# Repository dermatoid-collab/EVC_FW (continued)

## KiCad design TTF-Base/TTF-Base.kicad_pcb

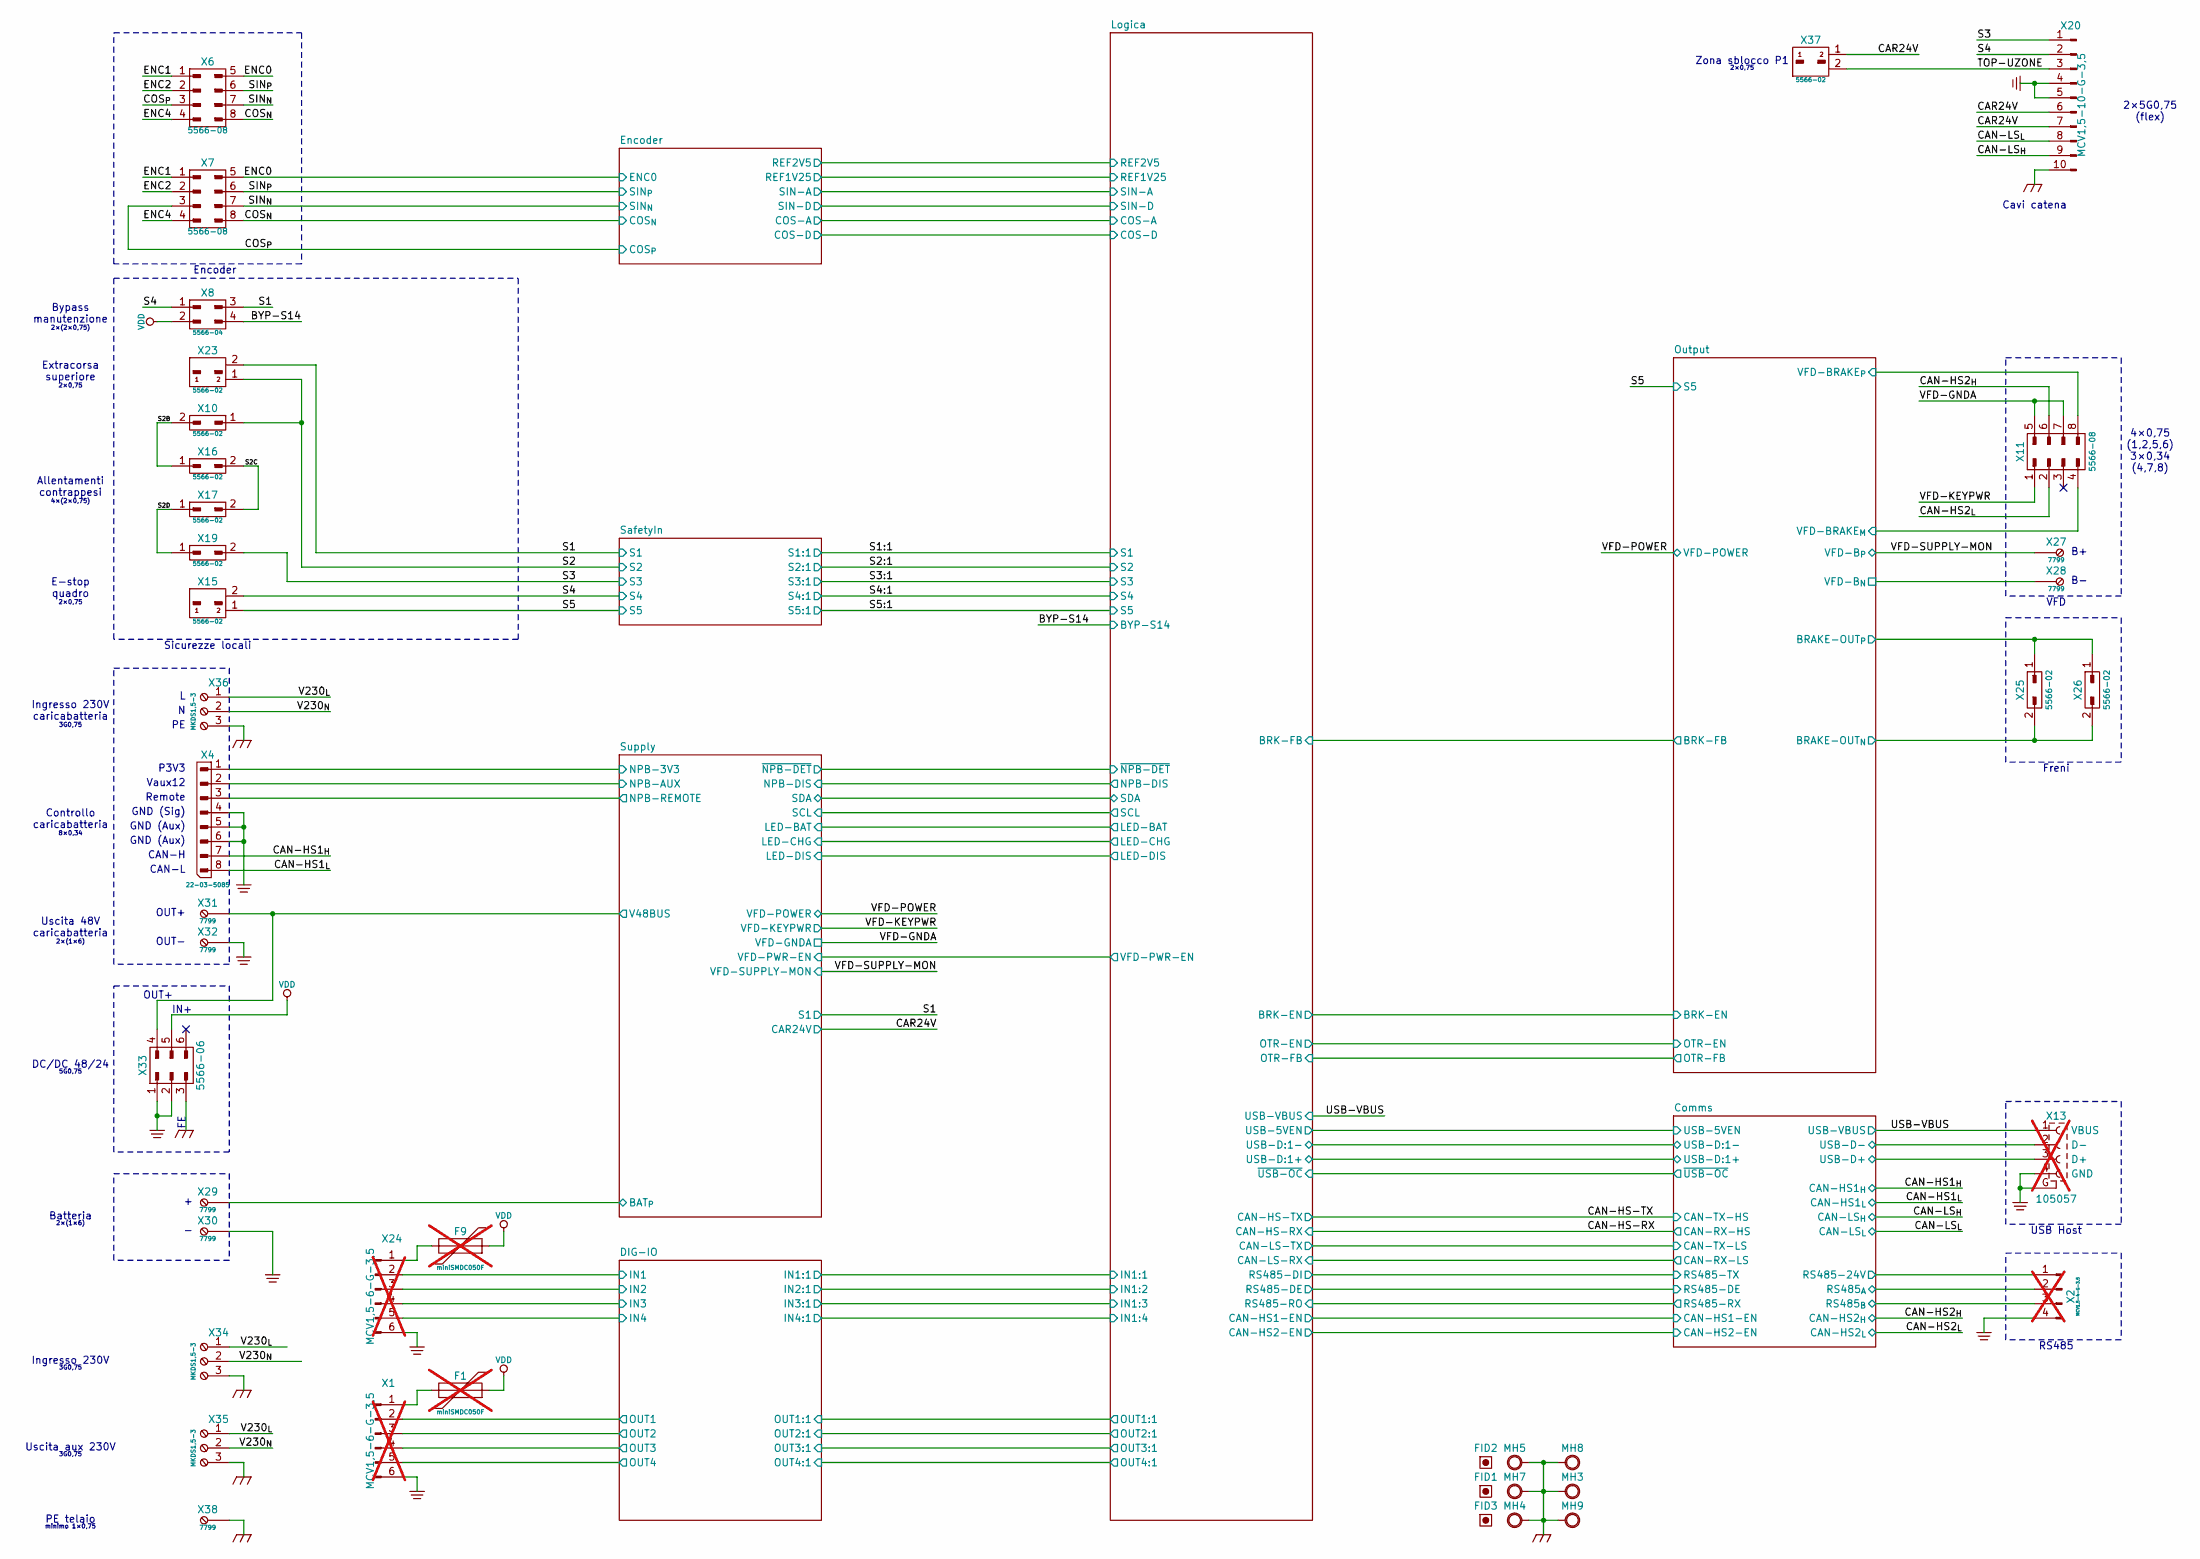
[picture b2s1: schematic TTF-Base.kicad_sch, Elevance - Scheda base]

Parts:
F1, F9: miniSMDC050F; miniSMDC; not fitted
FID1, FID2, FID3: Fiducial; Fid-10
MH3, MH4, MH5, MH7, MH8, MH9: Hole; Hole-M4
X1, X24: MCV1,5-6-G-3,5; not fitted
X2: MCV1,5-4-G-3,5; not fitted
X4: 22-03-5085
X6, X7, X11: 5566-08
X8: 5566-04
X10, X15, X16, X17, X19, X23, X25, X26, X37: 5566-02
X13: 105057; Molex-105057; not fitted
X20: MCV1,5-10-G-3,5
X27, X28, X29, X30, X31, X32, X38: 7799; Keystone-7799
X33: 5566-06
X34, X35, X36: MKDS1,5-3

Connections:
/BYP-S14: X8.4; also elsewhere on the board
/CAN-HS1_{H}: X4.7; also elsewhere on the board
/CAN-HS1_{L}: X4.8; also elsewhere on the board
/CAN-HS2_{H}: X11.6; also elsewhere on the board
/CAN-HS2_{L}: X11.2; also elsewhere on the board
/CAN-LS_{H}: X20.9; also elsewhere on the board
/CAN-LS_{L}: X20.8; also elsewhere on the board
/CAR24V: X20.6, X20.7, X37.1; also elsewhere on the board
/COS_{N}: X6.8, X7.8; also elsewhere on the board
/COS_{P}: X6.3, X7.3; also elsewhere on the board
/Comms/RS485-24V: X2.1; also elsewhere on the board
/Comms/RS485_{A}: X2.2; also elsewhere on the board
/Comms/RS485_{B}: X2.3; also elsewhere on the board
/Comms/USB-D+: X13.3 (D+); also elsewhere on the board
/Comms/USB-D-: X13.2 (D-); also elsewhere on the board
/DIG-IO/IN1: X24.2; also elsewhere on the board
/DIG-IO/IN2: X24.3; also elsewhere on the board
/DIG-IO/IN3: X24.4; also elsewhere on the board
/DIG-IO/IN4: X24.5; also elsewhere on the board
/DIG-IO/OUT1: X1.2; also elsewhere on the board
/DIG-IO/OUT2: X1.3; also elsewhere on the board
/DIG-IO/OUT3: X1.4; also elsewhere on the board
/DIG-IO/OUT4: X1.5; also elsewhere on the board
/ENC0: X6.5, X7.5; also elsewhere on the board
/ENC1: X6.1, X7.1
/ENC2: X6.2, X7.2
/ENC4: X6.4, X7.4
/Output/BRAKE-OUT_{N}: X25.2, X26.2; also elsewhere on the board
/Output/BRAKE-OUT_{P}: X25.1, X26.1; also elsewhere on the board
/Output/VFD-BRAKE_{M}: X11.4; also elsewhere on the board
/Output/VFD-BRAKE_{P}: X11.8; also elsewhere on the board
/Output/VFD-B_{N}: X28.1 (1_1); also elsewhere on the board
/S1: X8.3, X23.2; also elsewhere on the board
/S2: X10.1, X23.1; also elsewhere on the board
/S2B: X10.2, X16.1
/S2C: X16.2, X17.2
/S2D: X17.1, X19.1
/S3: X19.2, X20.1; also elsewhere on the board
/S4: X8.1, X15.2, X20.2; also elsewhere on the board
/S5: X15.1; also elsewhere on the board
/SIN_{N}: X6.7, X7.7; also elsewhere on the board
/SIN_{P}: X6.6, X7.6; also elsewhere on the board
/Supply/BAT_{P}: X29.1 (1_1); also elsewhere on the board
/Supply/NPB-3V3: X4.1; also elsewhere on the board
/Supply/NPB-AUX: X4.2; also elsewhere on the board
/Supply/NPB-REMOTE: X4.3; also elsewhere on the board
/Supply/V48BUS: X31.1 (1_1), X33.4; also elsewhere on the board
/TOP-UZONE: X20.3, X37.2
/USB-VBUS: X13.1 (VBUS); also elsewhere on the board
/V230_{L}: X34.1, X35.1, X36.1
/V230_{N}: X34.2, X35.2, X36.2
/VFD-GNDA: X11.5, X11.7; also elsewhere on the board
/VFD-KEYPWR: X11.1; also elsewhere on the board
/VFD-SUPPLY-MON: X27.1 (1_1); also elsewhere on the board
CHASSIS: MH3.HOLE (HOLE_HOLE), MH4.HOLE (HOLE_HOLE), MH5.HOLE (HOLE_HOLE), MH7.HOLE (HOLE_HOLE), MH8.HOLE (HOLE_HOLE), MH9.HOLE (HOLE_HOLE), X20.10, X33.3, X34.3, X35.3, X36.3, X38.1 (1_1)
GND: X1.6, X2.4, X4.4, X4.5, X4.6, X13.4 (GND), X13.G, X20.4, X20.5, X24.6, X30.1 (1_1), X32.1 (1_1), X33.1, X33.2; also elsewhere on the board
unnamed: F1.1, X1.1
unnamed: F9.1, X24.1
VDD: F1.2, F9.2, X8.2, X33.5; also elsewhere on the board

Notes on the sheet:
IN+
OUT-
4×0,75 (1,2,5,6) 3×0,34 (4,7,8)
Encoder
CAN-L
Ingresso 230V
GND (Aux)
5G0,75
PE telaio
2×(1×6)
Batteria
Allentamenti contrappesi
2×(2×0,75)
CAN-H
Extracorsa superiore
minimo 1×0,75
2×0,75
Vaux12
Freni
VFD
Ingresso 230V caricabatteria
E-stop quadro
2×5G0,75 (flex)
Bypass manutenzione
USB Host
3G0,75
Uscita aux 230V
OUT+
Zona sblocco P1
P3V3
8×0,34
RS485
DC/DC 48/24
Controllo caricabatteria
Cavi catena
Sicurezze locali
Uscita 48V caricabatteria
4×(2×0,75)
Remote
GND (Sig)

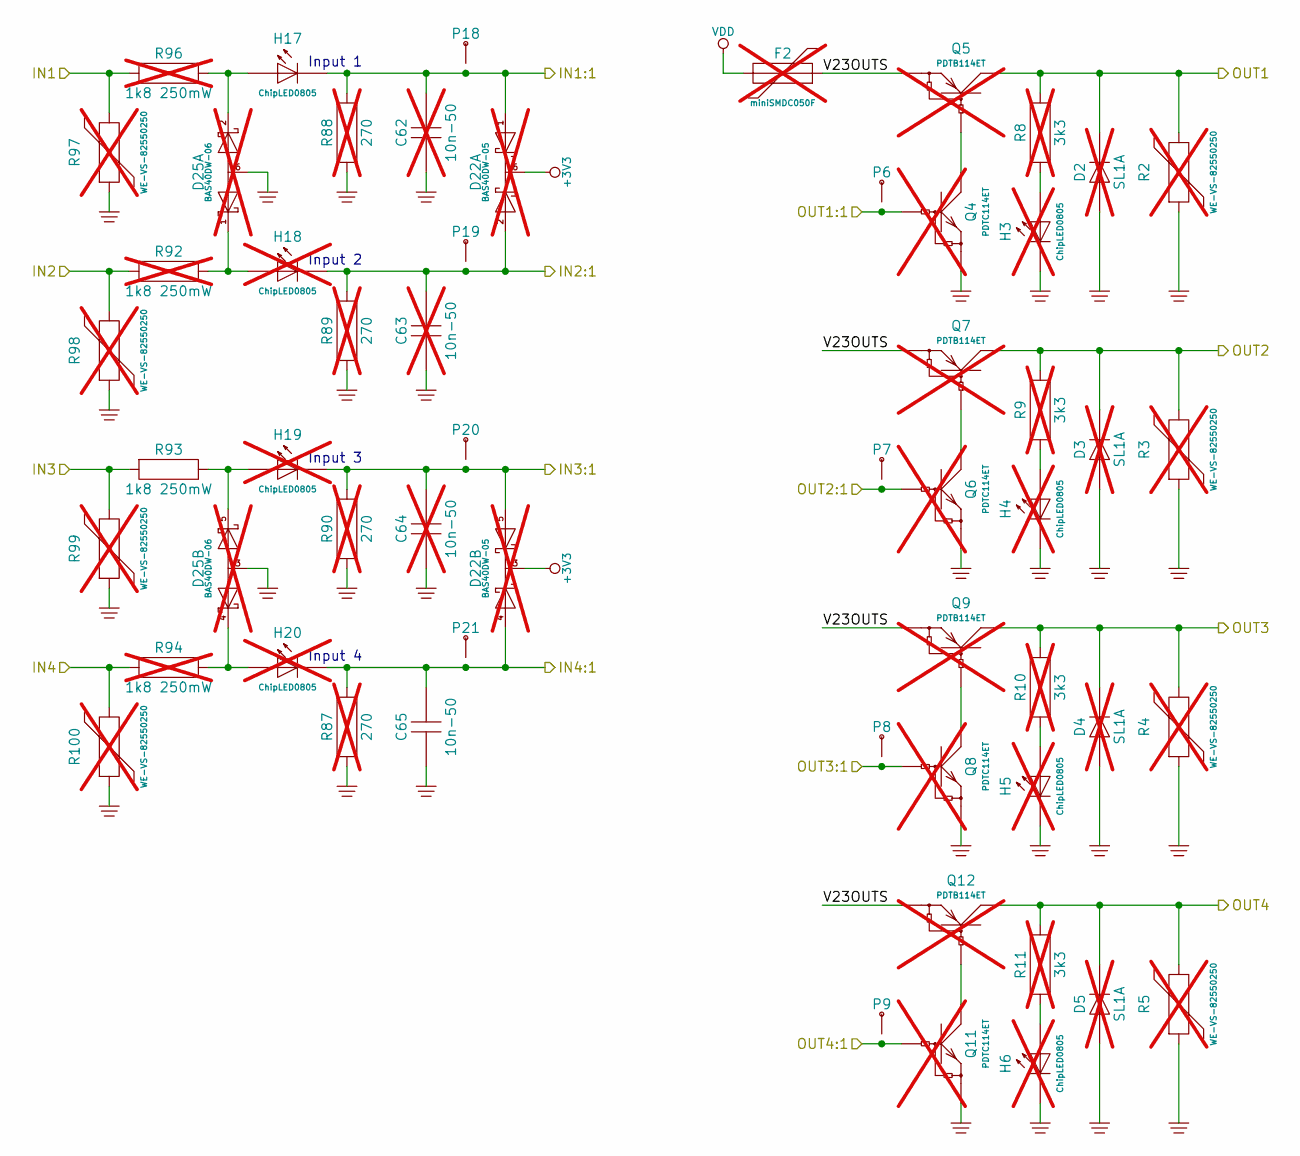
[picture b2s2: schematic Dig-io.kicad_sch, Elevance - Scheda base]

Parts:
C62, C63, C64: 10n-50; C0603; not fitted
C65: 10n-50; C0603
D2, D3, D4, D5: SL1A; SOD123FL; not fitted
D22: BAS40DW-05; MO203AB; not fitted
D25: BAS40DW-06; MO203AB; not fitted
F2: miniSMDC050F; miniSMDC; not fitted
H3, H4, H5, H6, H18, H19, H20: ChipLED0805; Chipled-0805; not fitted
H17: ChipLED0805; Chipled-0805
P6, P7, P8, P9, P18, P19, P20, P21: TestPoint; PinTst
Q4, Q6, Q8, Q11: PDTC114ET; TO236-BEC; not fitted
Q5, Q7, Q9, Q12: PDTB114ET; TO236-BEC; not fitted
R2, R3, R4, R5, R97, R98, R99, R100: WE-VS-82550250; WE-VS-0805; not fitted
R8, R9, R10, R11: 3k3; R1206; not fitted
R87, R88, R89, R90: 270; R0603; not fitted
R92, R94, R96: 1k8 250mW; R1206; not fitted
R93: 1k8 250mW; R1206

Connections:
+3V3: D22.3 (K), D22.6 (K); also elsewhere on the board
/DIG-IO/IN1: R96.2, R97.2; also elsewhere on the board
/DIG-IO/IN1:1: C62.2, D22.1 (A1), H17.K, P18.1 (P1_1), R88.1; also elsewhere on the board
/DIG-IO/IN2: R92.2, R98.2; also elsewhere on the board
/DIG-IO/IN2:1: C63.2, D22.2 (A2), H18.K, P19.1 (P1_1), R89.1; also elsewhere on the board
/DIG-IO/IN3: R93.2, R99.2; also elsewhere on the board
/DIG-IO/IN3:1: C64.2, D22.5 (A2), H19.K, P20.1 (P1_1), R90.1; also elsewhere on the board
/DIG-IO/IN4: R94.2, R100.2; also elsewhere on the board
/DIG-IO/IN4:1: C65.2, D22.4 (A1), H20.K, P21.1 (P1_1), R87.1; also elsewhere on the board
/DIG-IO/OUT1: D2.K, Q5.C, R2.2, R8.1; also elsewhere on the board
/DIG-IO/OUT1:1: P6.1 (P1_1), Q4.B; also elsewhere on the board
/DIG-IO/OUT2: D3.K, Q7.C, R3.2, R9.1; also elsewhere on the board
/DIG-IO/OUT2:1: P7.1 (P1_1), Q6.B; also elsewhere on the board
/DIG-IO/OUT3: D4.K, Q9.C, R4.2, R10.1; also elsewhere on the board
/DIG-IO/OUT3:1: P8.1 (P1_1), Q8.B; also elsewhere on the board
/DIG-IO/OUT4: D5.K, Q12.C, R5.2, R11.1; also elsewhere on the board
/DIG-IO/OUT4:1: P9.1 (P1_1), Q11.B; also elsewhere on the board
/DIG-IO/V23OUTS: F2.2, Q5.E, Q7.E, Q9.E, Q12.E
GND: C62.1, C63.1, C64.1, C65.1, D2.A, D3.A, D4.A, D5.A, D25.3 (A), D25.6 (A), H3.K, H4.K, H5.K, H6.K, Q4.E, Q6.E, Q8.E, Q11.E, R2.1, R3.1, R4.1, R5.1, R87.2, R88.2, R89.2, R90.2, R97.1, R98.1, R99.1, R100.1; also elsewhere on the board
unnamed: D25.1 (K1), H18.A, R92.1
unnamed: D25.2 (K2), H17.A, R96.1
unnamed: D25.4 (K1), H20.A, R94.1
unnamed: D25.5 (K2), H19.A, R93.1
unnamed: H3.A, R8.2
unnamed: H4.A, R9.2
unnamed: H5.A, R10.2
unnamed: H6.A, R11.2
unnamed: Q4.C, Q5.B
unnamed: Q6.C, Q7.B
unnamed: Q8.C, Q9.B
unnamed: Q11.C, Q12.B
VDD: F2.1; also elsewhere on the board

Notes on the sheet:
Input 2
Input 4
Input 1
Input 3

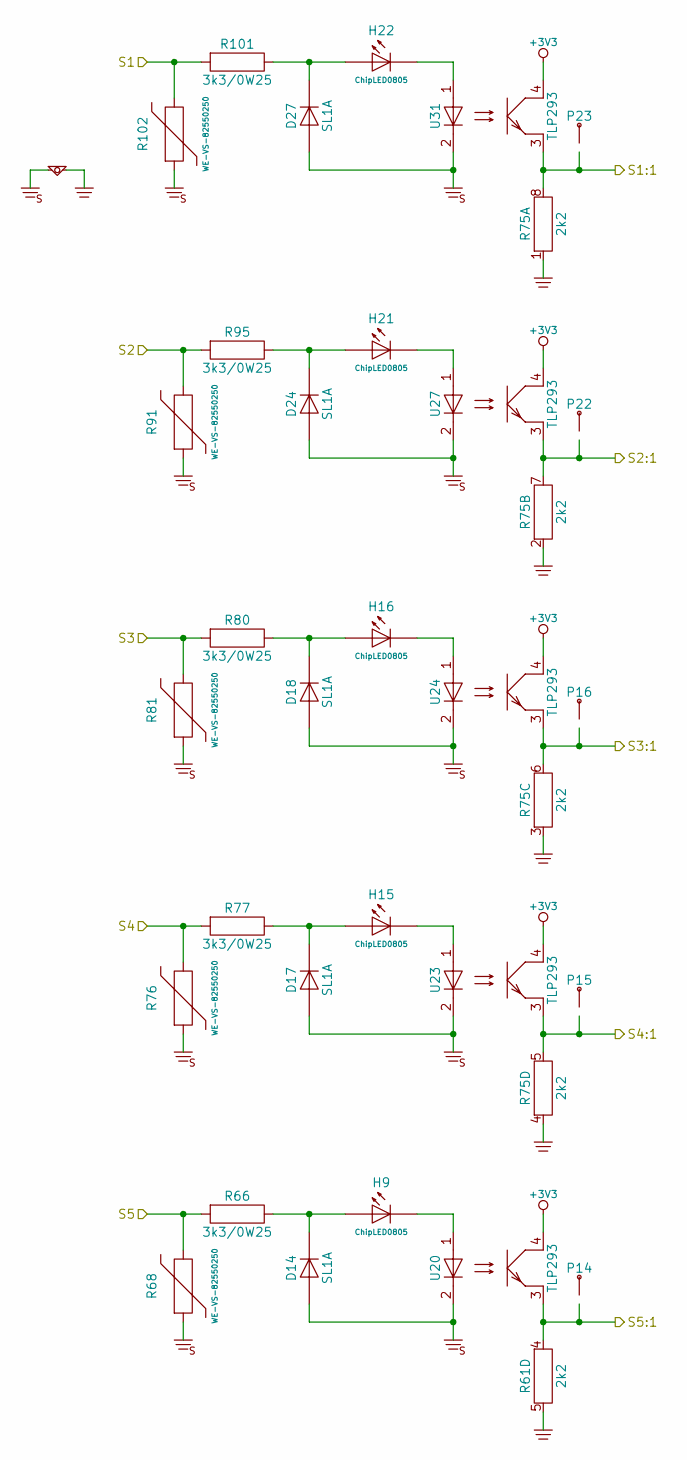
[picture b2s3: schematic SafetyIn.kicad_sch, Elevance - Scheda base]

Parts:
D14, D17, D18, D24, D27: SL1A; SOD123FL
EQUI3: EQUIPOT; Equipot-04
H9, H15, H16, H21, H22: ChipLED0805; Chipled-0805
P14, P15, P16, P22, P23: TestPoint; PinTst
R61, R75: 2k2; KMY-RAC164D
R66, R77, R80, R95, R101: 3k3/0W25; R1206
R68, R76, R81, R91, R102: WE-VS-82550250; WE-VS-0805
U20, U23, U24, U27, U31: TLP293; Toshiba-11-3C1

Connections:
+3V3: U20.4 (C), U23.4 (C), U24.4 (C), U27.4 (C), U31.4 (C); also elsewhere on the board
/S1: R101.2, R102.2; also elsewhere on the board
/S1:1: P23.1 (P1_1), R75.8, U31.3 (E); also elsewhere on the board
/S2: R91.2, R95.2; also elsewhere on the board
/S2:1: P22.1 (P1_1), R75.7, U27.3 (E); also elsewhere on the board
/S3: R80.2, R81.2; also elsewhere on the board
/S3:1: P16.1 (P1_1), R75.6, U24.3 (E); also elsewhere on the board
/S4: R76.2, R77.2; also elsewhere on the board
/S4:1: P15.1 (P1_1), R75.5, U23.3 (E); also elsewhere on the board
/S5: R66.2, R68.2; also elsewhere on the board
/S5:1: P14.1 (P1_1), R61.4, U20.3 (E); also elsewhere on the board
GND: EQUI3.2, R61.5, R75.1, R75.2, R75.3, R75.4; also elsewhere on the board
GNDS: D14.A, D17.A, D18.A, D24.A, D27.A, EQUI3.1, R68.1, R76.1, R81.1, R91.1, R102.1, U20.2 (K), U23.2 (K), U24.2 (K), U27.2 (K), U31.2 (K)
unnamed: D14.K, H9.A, R66.1
unnamed: D17.K, H15.A, R77.1
unnamed: D18.K, H16.A, R80.1
unnamed: D24.K, H21.A, R95.1
unnamed: D27.K, H22.A, R101.1
unnamed: H9.K, U20.1 (A)
unnamed: H15.K, U23.1 (A)
unnamed: H16.K, U24.1 (A)
unnamed: H21.K, U27.1 (A)
unnamed: H22.K, U31.1 (A)

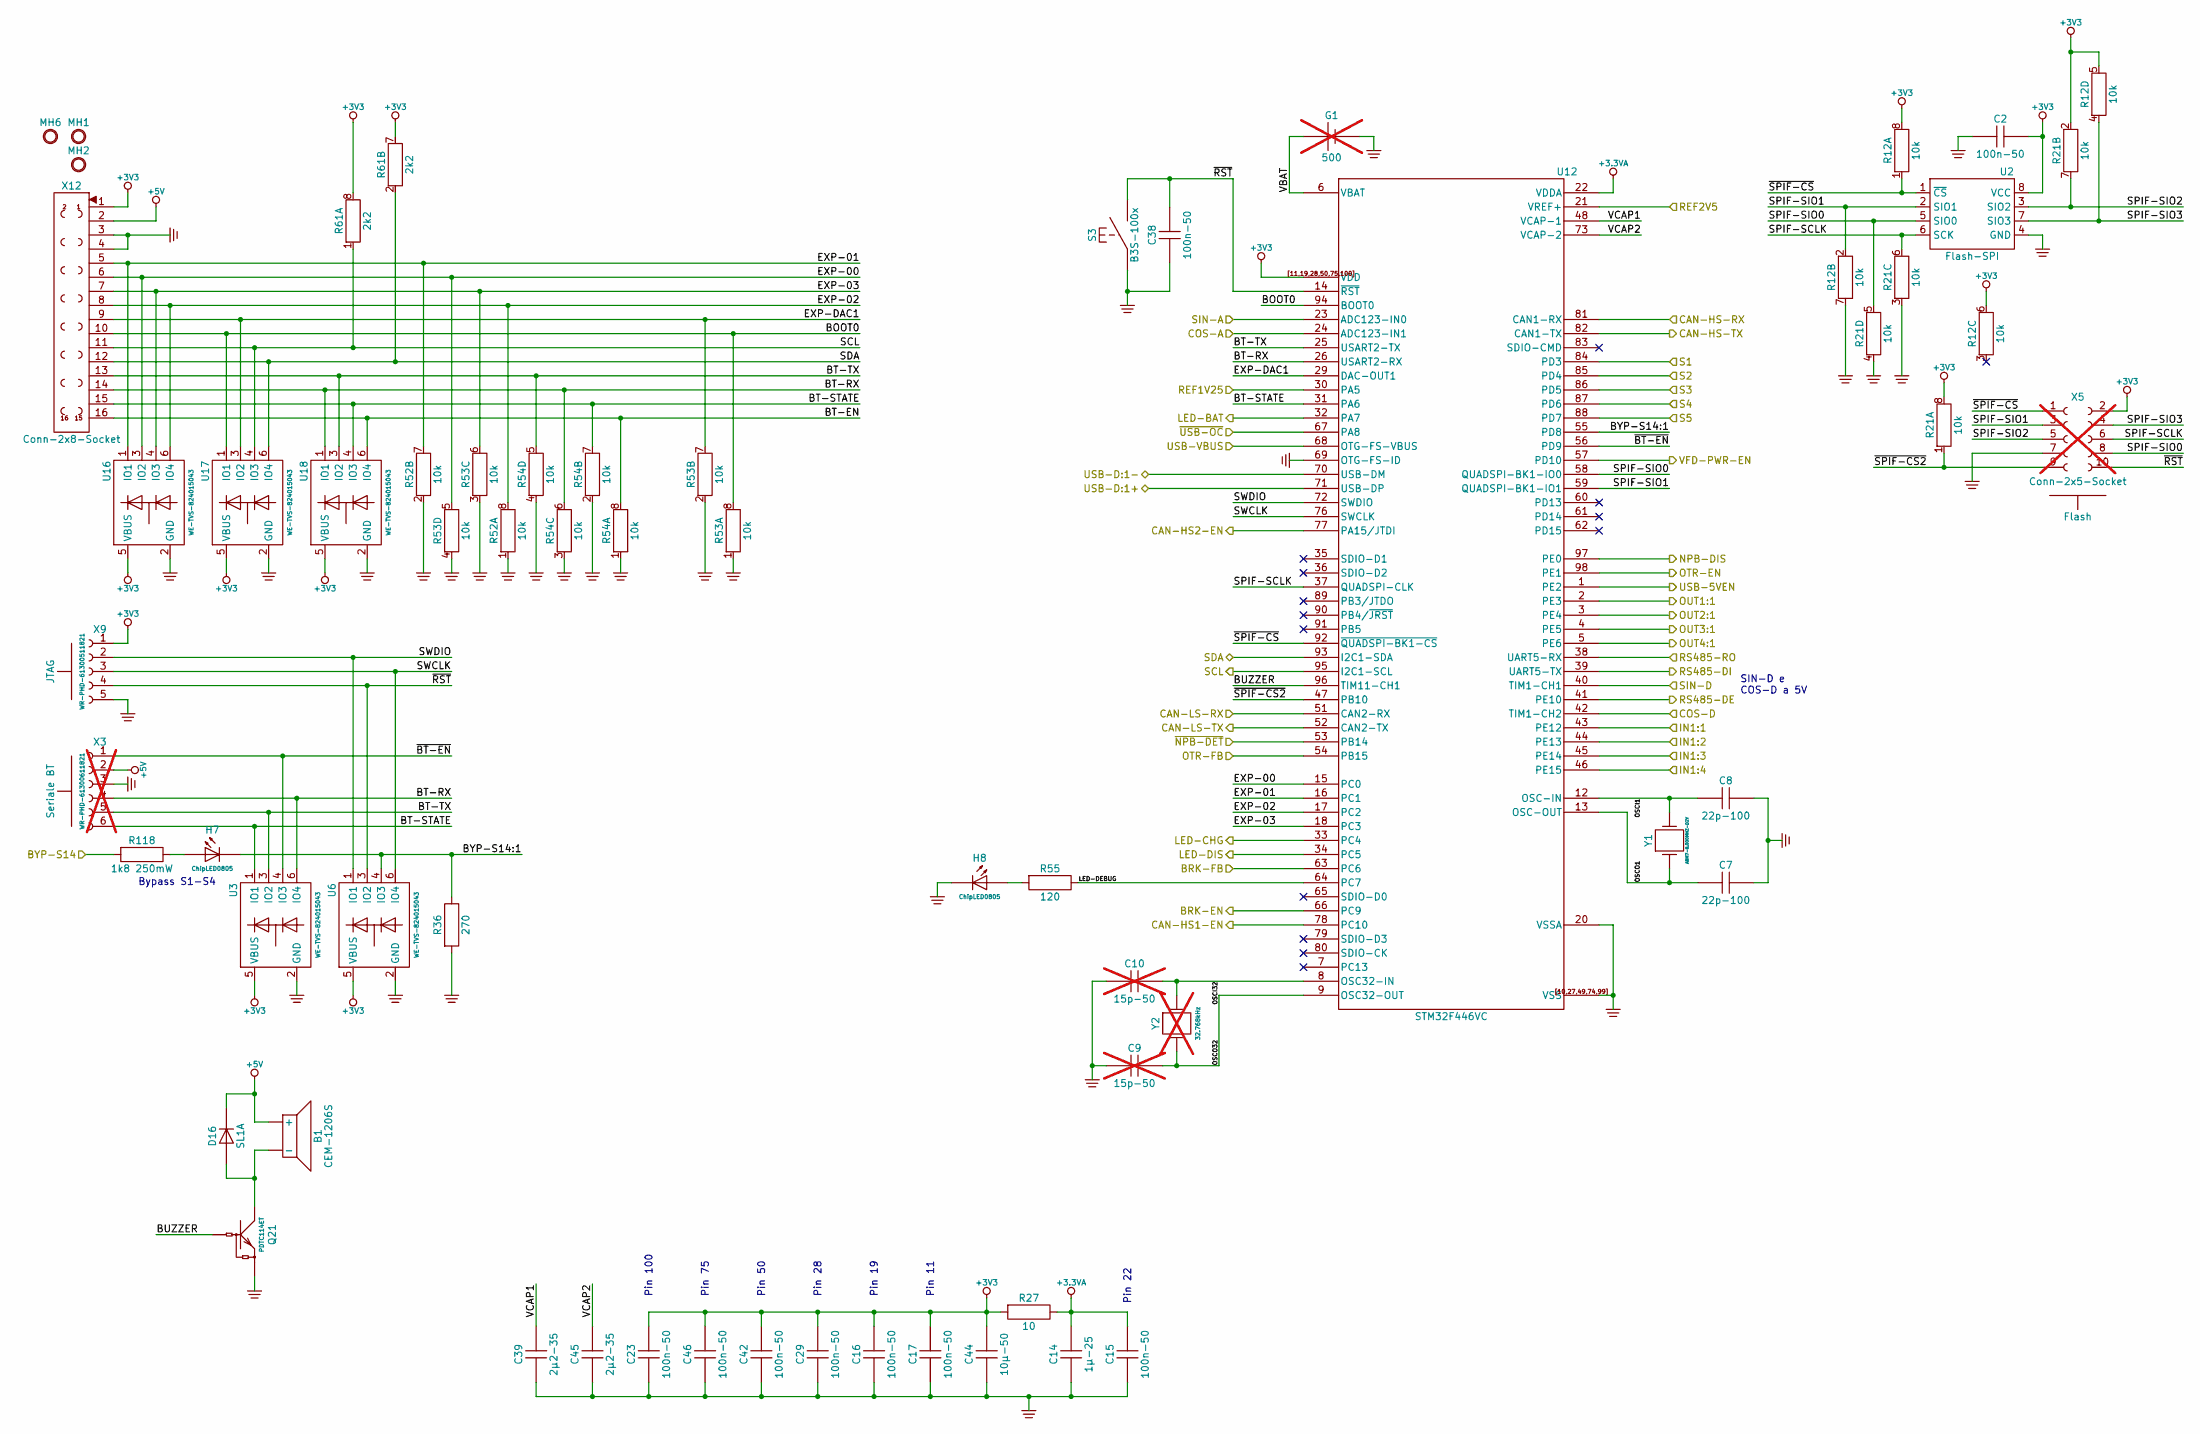
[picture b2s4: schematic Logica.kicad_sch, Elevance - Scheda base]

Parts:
B1: CEM-1206S; CUI-CEM-1206S
C2, C15, C16, C17, C23, C29, C38, C42, C46: 100n-50; C0603
C7, C8: 22p-100; C0603
C9, C10: 15p-50; C0603; not fitted
C14: 1µ-25; C0603
C39, C45: 2µ2-35; C0603
C44: 10µ-50; C1206
D16: SL1A; SOD123FL
G1: 500; Keystone-500; not fitted
H7, H8: ChipLED0805; Chipled-0805
MH1, MH2, MH6: Hole-M3; Hole-M3-NoPad-HeadOnly
Q21: PDTC114ET; TO236-BEC
R12, R21, R52, R53, R54: 10k; KMY-RAC164D
R27: 10; R0603
R36: 270; R0603
R55: 120; R0603
R61: 2k2; KMY-RAC164D
R118: 1k8 250mW; R1206
S3: B3S-100x; Omron-B3S-100x
U2: Flash-SPI; MS012AA+208mil
U3, U6, U16, U17, U18: WE-TVS-824015043; MO178AB
U12: STM32F446VC; MS026BED
X3: WR-PHD-61300611821; F-6; not fitted
X5: Conn-2x5-Socket; F-2x5; not fitted
X9: WR-PHD-61300511821; F-5
X12: Conn-2x8-Socket; F-2x8
Y1: ABM7-8.000MHZ-D2Y; Abracon-ABM07
Y2: 32.768kHz; Abracon-ABS07; not fitted
ZZZ4: JTAG
ZZZ5: Seriale BT
ZZZ6: Flash

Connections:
+3.3VA: C14.2, C15.2, R27.1, U12.22 (VDDA)
+3V3: C2.2, C16.2, C17.2, C23.2, C29.2, C42.2, C44.2, C46.2, R12.5, R12.6, R12.8, R21.2, R21.8, R27.2, R61.7, R61.8, U2.8 (VCC), U3.5 (VBUS), U6.5 (VBUS), U12.11 (VDD), U12.19 (VDD), U12.28 (VDD), U12.50 (VDD), U12.75 (VDD), U12.100 (VDD), U12.[11,19,28,50,75,100] (VDD), U16.5 (VBUS), U17.5 (VBUS), U18.5 (VBUS), X5.2, X9.1, X12.1; also elsewhere on the board
+5V: B1.+, D16.K, X3.2, X12.2; also elsewhere on the board
/BYP-S14: R118.2; also elsewhere on the board
/CAN-HS-RX: U12.81 (CAN1-RX); also elsewhere on the board
/CAN-HS-TX: U12.82 (CAN1-TX); also elsewhere on the board
/Comms/CAN-HS1-EN: U12.78 (PC10); also elsewhere on the board
/Comms/CAN-HS2-EN: U12.77 (PA15/JTDI); also elsewhere on the board
/Comms/CAN-RX-LS: U12.51 (CAN2-RX); also elsewhere on the board
/Comms/CAN-TX-LS: U12.52 (CAN2-TX); also elsewhere on the board
/Comms/RS485-DE: U12.41 (PE10); also elsewhere on the board
/Comms/RS485-RX: U12.38 (UART5-RX); also elsewhere on the board
/Comms/RS485-TX: U12.39 (UART5-TX); also elsewhere on the board
/Comms/USB-5VEN: U12.1 (PE2); also elsewhere on the board
/Comms/USB-D:1+: U12.71 (USB-DP); also elsewhere on the board
/Comms/USB-D:1-: U12.70 (USB-DM); also elsewhere on the board
/Comms/~USB-OC: U12.67 (PA8); also elsewhere on the board
/DIG-IO/IN1:1: U12.43 (PE12); also elsewhere on the board
/DIG-IO/IN2:1: U12.44 (PE13); also elsewhere on the board
/DIG-IO/IN3:1: U12.45 (PE14); also elsewhere on the board
/DIG-IO/IN4:1: U12.46 (PE15); also elsewhere on the board
/DIG-IO/OUT1:1: U12.2 (PE3); also elsewhere on the board
/DIG-IO/OUT2:1: U12.3 (PE4); also elsewhere on the board
/DIG-IO/OUT3:1: U12.4 (PE5); also elsewhere on the board
/DIG-IO/OUT4:1: U12.5 (PE6); also elsewhere on the board
/Encoder/COS-A: U12.24 (ADC123-IN1); also elsewhere on the board
/Encoder/COS-D: U12.42 (TIM1-CH2); also elsewhere on the board
/Encoder/REF1V25: U12.30 (PA5); also elsewhere on the board
/Encoder/REF2V5: U12.21 (VREF+); also elsewhere on the board
/Encoder/SIN-A: U12.23 (ADC123-IN0); also elsewhere on the board
/Encoder/SIN-D: U12.40 (TIM1-CH1); also elsewhere on the board
/Logica/BOOT0: R53.8, U12.94 (BOOT0), U17.1 (IO1), X12.10
/Logica/BRK-EN: U12.66 (PC9); also elsewhere on the board
/Logica/BRK-FB: U12.63 (PC6); also elsewhere on the board
/Logica/BT-EN: R54.8, U18.6 (IO4), X12.16
/Logica/BT-RX: R54.6, U3.6 (IO4), U12.26 (USART2-RX), U18.1 (IO1), X3.4, X12.14
/Logica/BT-STATE: R54.7, U3.1 (IO1), U12.31 (PA6), U18.4 (IO3), X3.6, X12.15
/Logica/BT-TX: R54.5, U3.3 (IO2), U12.25 (USART2-TX), U18.3 (IO2), X3.5, X12.13
/Logica/BUZZER: Q21.B, U12.96 (TIM11-CH1)
/Logica/BYP-S14:1: H7.K, R36.1, U6.4 (IO3), U12.55 (PD8)
/Logica/EXP-00: R53.5, U12.15 (PC0), U16.3 (IO2), X12.6
/Logica/EXP-01: R52.7, U12.16 (PC1), U16.1 (IO1), X12.5
/Logica/EXP-02: R52.8, U12.17 (PC2), U16.6 (IO4), X12.8
/Logica/EXP-03: R53.6, U12.18 (PC3), U16.4 (IO3), X12.7
/Logica/EXP-DAC1: R53.7, U12.29 (DAC-OUT1), U17.3 (IO2), X12.9
/Logica/LED-BAT: U12.32 (PA7); also elsewhere on the board
/Logica/LED-CHG: U12.33 (PC4); also elsewhere on the board
/Logica/LED-DEBUG: R55.1, U12.64 (PC7)
/Logica/LED-DIS: U12.34 (PC5); also elsewhere on the board
/Logica/NPB-DIS: U12.97 (PE0); also elsewhere on the board
/Logica/OSCI1: C8.2, U12.12 (OSC-IN), Y1.2
/Logica/OSCI32: C10.2, U12.8 (OSC32-IN), Y2.1
/Logica/OSCO1: C7.2, U12.13 (OSC-OUT), Y1.1
/Logica/OSCO32: C9.2, U12.9 (OSC32-OUT), Y2.2
/Logica/OTR-EN: U12.98 (PE1); also elsewhere on the board
/Logica/OTR-FB: U12.54 (PB15); also elsewhere on the board
/Logica/SCL: R61.1, U12.95 (I2C1-SCL), U17.4 (IO3), X12.11; also elsewhere on the board
/Logica/SDA: R61.2, U12.93 (I2C1-SDA), U17.6 (IO4), X12.12; also elsewhere on the board
/Logica/SPIF-SCLK: R21.6, U2.6 (SCK), U12.37 (QUADSPI-CLK), X5.6
/Logica/SPIF-SIO0: R21.5, U2.5 (SIO0), U12.58 (QUADSPI-BK1-IO0), X5.8
/Logica/SPIF-SIO1: R12.2, U2.2 (SIO1), U12.59 (QUADSPI-BK1-IO1), X5.3
/Logica/SPIF-SIO2: R21.7, U2.3 (SIO2), X5.5
/Logica/SPIF-SIO3: R12.4, U2.7 (SIO3), X5.4
/Logica/SWCLK: U6.6 (IO4), U12.76 (SWCLK), X9.3
/Logica/SWDIO: U6.1 (IO1), U12.72 (SWDIO), X9.2
/Logica/VBAT: G1.+, U12.6 (VBAT)
/Logica/VCAP1: C39.2, U12.48 (VCAP-1)
/Logica/VCAP2: C45.2, U12.73 (VCAP-2)
/Logica/VFD-PWR-EN: U12.57 (PD10); also elsewhere on the board
/Logica/~BT-EN: U3.4 (IO3), U12.56 (PD9), X3.1
/Logica/~NPB-DET: U12.53 (PB14); also elsewhere on the board
/Logica/~RST: C38.2, S3.14, U6.3 (IO2), U12.14 (~RST), X5.10, X9.4
/Logica/~SPIF-CS2: R21.1, U12.47 (PB10), X5.9
/Logica/~SPIF-CS: R12.1, U2.1 (~CS), U12.92 (~QUADSPI-BK1-CS), X5.1
/S1:1: U12.84 (PD3); also elsewhere on the board
/S2:1: U12.85 (PD4); also elsewhere on the board
/S3:1: U12.86 (PD5); also elsewhere on the board
/S4:1: U12.87 (PD6); also elsewhere on the board
/S5:1: U12.88 (PD7); also elsewhere on the board
/USB-VBUS: U12.68 (OTG-FS-VBUS); also elsewhere on the board
GND: C2.1, C7.1, C8.1, C9.1, C10.1, C14.1, C15.1, C16.1, C17.1, C23.1, C29.1, C38.1, C39.1, C42.1, C44.1, C45.1, C46.1, G1.-, H8.K, Q21.E, R12.7, R21.3, R21.4, R36.2, R52.1, R52.2, R53.1, R53.2, R53.3, R53.4, R54.1, R54.2, R54.3, R54.4, S3.13, U2.4 (GND), U3.2 (GND), U6.2 (GND), U12.10 (VSS), U12.20 (VSSA), U12.27 (VSS), U12.49 (VSS), U12.69 (OTG-FS-ID), U12.74 (VSS), U12.99 (VSS), U12.[10,27,49,74,99] (VSS), U16.2 (GND), U17.2 (GND), U18.2 (GND), X3.3, X5.7, X9.5, X12.3, X12.4; also elsewhere on the board
unnamed: B1.-, D16.A, Q21.C
unnamed: H7.A, R118.1
unnamed: H8.A, R55.2

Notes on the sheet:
Pin 28
SIN-D e COS-D a 5V
Pin 19
Pin 75
Pin 11
Pin 100
Pin 50
Pin 22
Bypass S1-S4
